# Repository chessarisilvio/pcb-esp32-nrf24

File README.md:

pcb-esp32-nrf24

This project is made to make two esp32 communicate on the 2.4ghz band with 2 nrf24 ebyte in the range of 50m.
you can then show the text on a esp32 Yellow board or on a 0.96 OLED screen connected to the esp32.
It’s perfect for experimenting with wireless communication.

What You Need (Per Node)
- 1× ESP32 DevKit board (38-pin, with USB Type-C)
- 2× nRF24L01 modules (E-BYTE version recommended)
- 1× ESP32 yellow display board (2.8" TFT with ILI9341 controller) OR a ssd1306 i2c OLED 0.96" screen
- 2× LM2596-3.3V DC-DC step-down converters (5V to 3.3V)
- At least 2 standard breadboards (or if assembling custom, 2 sets of 2.54mm female headers and 1 universal prototype board)
- 20× male-to-male jumper wires (20cm)
- 20× female-to-female jumper wires (20cm)
- Power supply: USB Type-C cable or a 5V battery pack

Wiring: Connect Each ESP32 to nRF24
nRF24L01 #1 Connections:
GND  -> GND
VCC  -> 3.3V
CE   -> GPIO17
CSN  -> GPIO5
SCK  -> GPIO18
MOSI -> GPIO23
MISO -> GPIO19

nRF24L01 #2 Connections:
GND  -> GND
VCC  -> 3.3V
CE   -> GPIO18
CSN  -> GPIO21
SCK  -> GPIO18
MOSI -> GPIO23
MISO -> GPIO19

Step 1: Install Required Libraries
In Arduino IDE, go to Sketch → Include Library → Manage Libraries and install:
- RF24 by TMRh20
- TFT_eSPI by Bodmer

Step 2: Configure TFT_eSPI Library
Find the TFT_eSPI folder:
- Windows: Documents\Arduino\libraries\TFT_eSPI
- Mac: ~/Documents/Arduino/libraries/TFT_eSPI
- Linux: ~/Arduino/libraries/TFT_eSPI
Open User_Setup_Select.h. Comment out all the #include lines except the one for your display. For the ESP32 yellow board with ILI9341, use:

for the c++ code:
#include <User_Setups/Setup25_TTGO_T_Display.h>

Step 3: Assemble Hardware
Node A: ESP32 #1 + nRF24 (with pins as above) + ESP32 Yellow Display #1

Node B: ESP32 #2 + nRF24 (same pins) + ESP32 Yellow Display #2

Step 4: Upload Code to Display Boards
Open display code in Arduino IDE.

Update your WiFi credentials:
On the c++ code find this two variables and give them the name and password of your wifi
const char* ssid = "YourWiFiName";
const char* password = "YourWiFiPassword";

For Display A, set String nodeID = "Display A";
For Display B, set String nodeID = "Display B";

then upload to each display board and open Serial Monitor (115200 baud) and note each display’s IP address.

Step 5:
Upload Code to nRF24 Boards, the update WiFi and set Display A’s IP address:
- const char* myDisplayIP = "192.168.1.100";  // Use your actual IP
- Upload to ESP32 with nRF24 (Node A) and check Serial Monitor for connection status.
- Repeat for Node B, using Display B’s IP address.

Step 6: Test the System
- Automatic test: Node A sends a message every 5 seconds, Node B every 7 seconds, and displays update automatically.

Manual test via web:
- Find Node A’s nRF24 IP from Serial Monitor.
- Open browser: http://[NodeA_IP]:8080
- Type a message, click "Send via nRF24," and see it appear on Node B’s display.
- Repeat from Node B to Node A.

Step 7: Verify Operation
Expected Serial Monitor output on Node A:

text
=== Node A: ESP32 with nRF24 ===
nRF24 initialized successfully
Connecting to WiFi.....
WiFi connected!
IP address: 192.168.1.102
Web server started on port 8080
Sending via nRF24: Node A: 5s - SUCCESS
=================================
nRF24 RECEIVED: Node B: 7s
=================================
Display update: HTTP 200

Expected display behavior:
- Shows received messages in large white text.
- Background refreshes on new messages.
- Footer displays IP address and uptime.

Troubleshooting
nRF24 initialization failed?
- Check all 7 connections (VCC, GND, CE, CSN, SCK, MOSI, MISO).
- Make sure nRF24 is powered from 3.3V, not 5V.
- Add a 10µF capacitor between VCC and GND on the nRF24.
- Try another nRF24 module (some may be defective).

WiFi connection timeout?
- Confirm SSID and password are correct.
- Router must be 2.4GHz (ESP32 doesn’t support 5GHz).
- Move closer to the router.
- Check router firewall settings.

Display shows "WiFi Failed"?
- Double-check credentials (case-sensitive).
- Confirm WiFi network is available.
- Try connecting via a phone hotspot.

Messages don’t appear on display?
- Verify display IP matches IP in nRF24 code.
- Ping display IP from a computer.
- Check Serial Monitor for HTTP errors.

nRF24 receives no data?
- Verify matching TX and RX addresses.
- Ensure modules are on the same channel.
- Reduce distance (start close, ~1 meter).
- Use the same data rate (RF24_250KBPS).

Display text looks corrupted?
- Reconfigure TFT_eSPI for your display.
- Check display wiring.
- Update TFT_eSPI library.

Web interface inaccessible?
- Check ESP32 IP in Serial Monitor.
- Use correct ports (:8080 for nRF24, :80 for displays).
- Disable or adjust computer firewall.

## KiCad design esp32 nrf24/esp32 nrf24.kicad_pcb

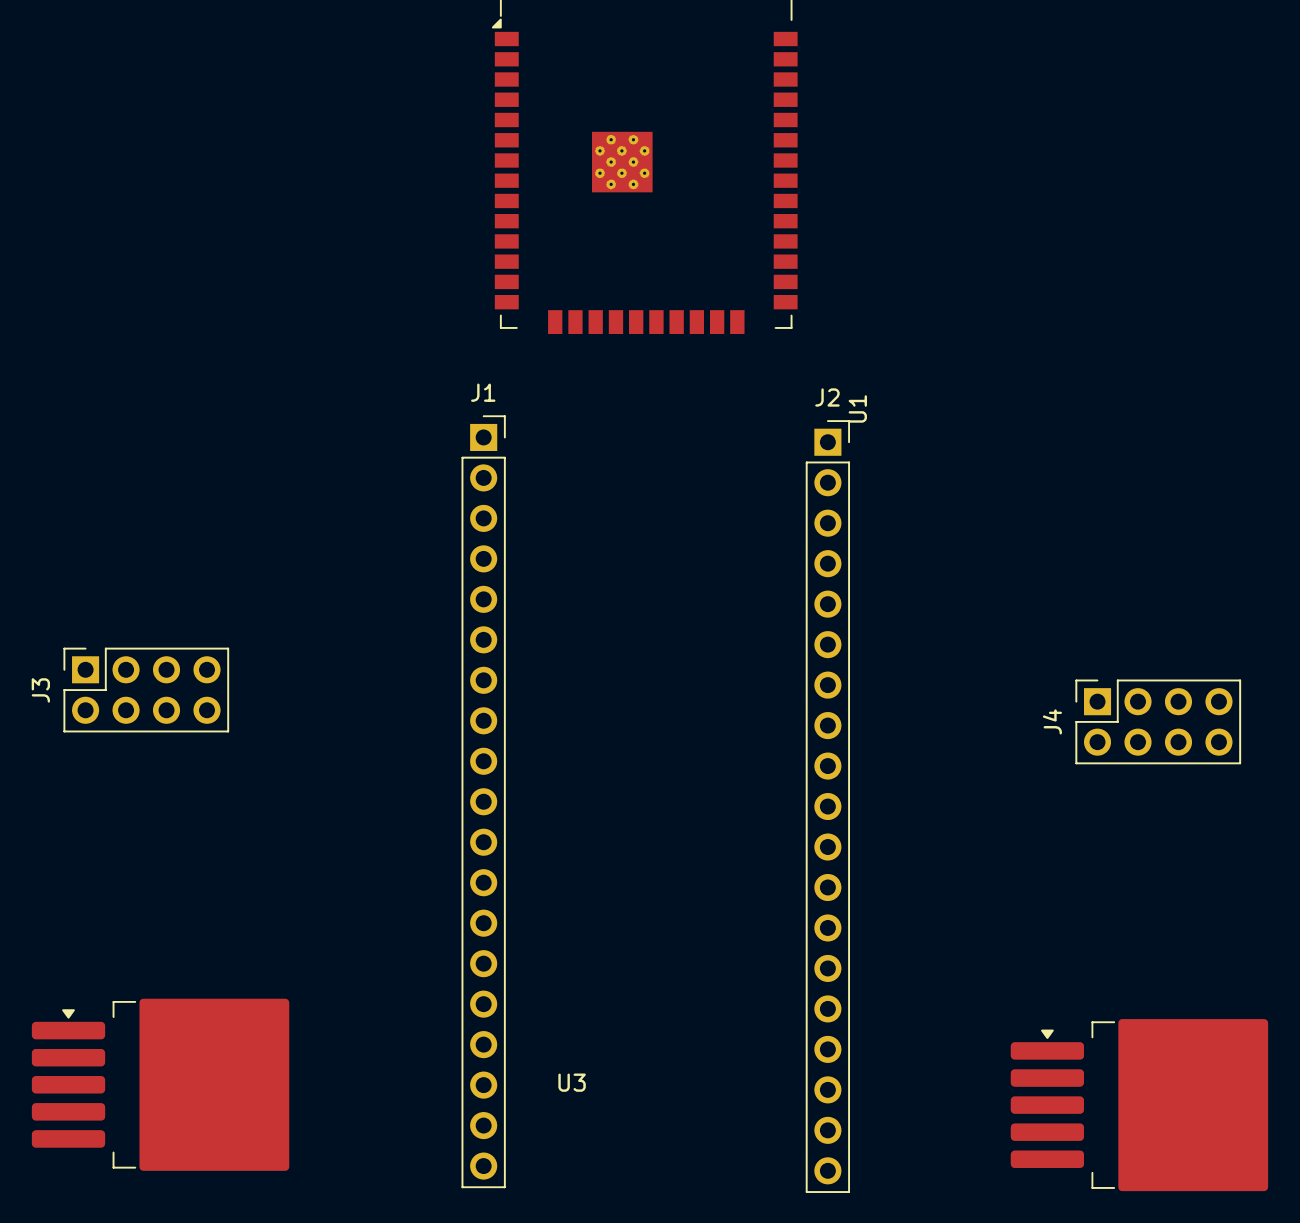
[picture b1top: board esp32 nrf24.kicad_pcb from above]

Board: 2 copper layers, 7 parts (0 on the bottom side), 4 nets, no tracks yet.

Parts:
J1, J2: Conn_01x19_Socket; PinSocket_1x19_P2.54mm_Vertical
J3, J4: Conn_01x04_Socket; PinSocket_2x04_P2.54mm_Vertical
U1: ESP32-WROOM-32D
U2, U3: LM2596S-3.3; TO-263-5_TabPin3

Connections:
+3.3V: J4.1, U2.2 (OUT), U3.2 (OUT)
+5V: J1.19, U2.1 (VIN), U3.1 (VIN)
GND: J1.14, J2.1, J2.7, J3.1, U2.3 (GND), U3.3 (GND)
unnamed: U1.1 (GND), U1.15 (GND), U1.38 (GND), U1.39 (GND)

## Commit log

2025-10-21 start of the esp32 nrf24 pcb
2025-10-22 photo of the connections
    i know this looks a bit messy but this should clean things:
    nRF24L01#1 Pin ESP32 Pin nRF24L01#2 Pin ESP32 Pin Note
    GND GND GND GND Shared by both modules
    VCC 3.3V VCC 3.3V Shared by both modules
    CE GPIO17 CE GPIO18 Use separate GPIO for each
    CSN GPIO5 CSN GPIO21 Use separate GPIO for each
2025-10-23 Implement nRF24 data receiver and WiFi sender
    This code sets up an ESP32 to receive data via nRF24 and send it to a specified server over WiFi.
2025-10-23 Add ESP32 NRF24 receiver with TFT display
    this is where you can see the text
2025-10-23 Update README with hardware requirements and connections
    Added hardware requirements and connection details for ESP32 and nRF24L01 modules.
2025-10-23 Enhance ESP32 nRF24 sender with web server support
    Refactor ESP32 nRF24 sender code to improve functionality and add web server for message handling.
2025-10-23 Refactor ESP32 nRF24 receiver with web interface
    Refactored ESP32 nRF24 receiver code to enhance functionality and web interface. Removed TFT display initialization and added web server handling for sending messages.
2025-10-23 Rename esp32 nrf24 sender to esp32 nrf24 NODE A
2025-10-23 Rename esp32 nrf24 + esp32 yellow display receiver to esp32 nrf24 NODE B
2025-10-23 Add ESP32 display board with WiFi and server setup
    Initial implementation of ESP32 display board with WiFi connectivity and HTTP server functionality.
2025-10-23 Expand README with setup and troubleshooting guide
    Added detailed setup instructions for using ESP32 with nRF24 and TFT_eSPI, including library installation, hardware assembly, code upload, testing, troubleshooting, and advanced customization options.
2025-10-23 Add LM2596-3.3 power converters to README
    Added two 5v to 3.3v LM2596-3.3 power converters to the list of components.
2025-10-23 Revise hardware requirements in README.md
    Updated hardware requirements and added details for each node.
2025-10-23 cvs file of the parts
2025-10-24 Revise README with detailed setup and troubleshooting
    Updated project description and hardware requirements. Added wiring instructions, setup steps, troubleshooting guide, and advanced customization options.
2025-10-24 Refactor Node A code for clarity and efficiency
2025-10-24 Refactor Node B code for clarity and consistency
2025-10-24 Refactor ESP32 display board code and comments
2025-10-24 Modify bom.csv with updated item specifications
    Updated specifications for the ESP32 Yellow Display Board.
2025-10-24 Update BOM file format and add missing header
2025-10-24 Update comments for OLED display connections
2025-10-24 Add External WiFi Antenna to BOM
    Added a new item 'External WiFi Antenna' to the BOM.
2025-10-24 Fix BOM formatting and update antenna description
2025-10-24 Update README with project image and description
    Added an image to the README and provided project details.
2026-06-07 fix: rimozione info personali e aggiornamento .gitignore
2026-06-07 chore: add MIT license
